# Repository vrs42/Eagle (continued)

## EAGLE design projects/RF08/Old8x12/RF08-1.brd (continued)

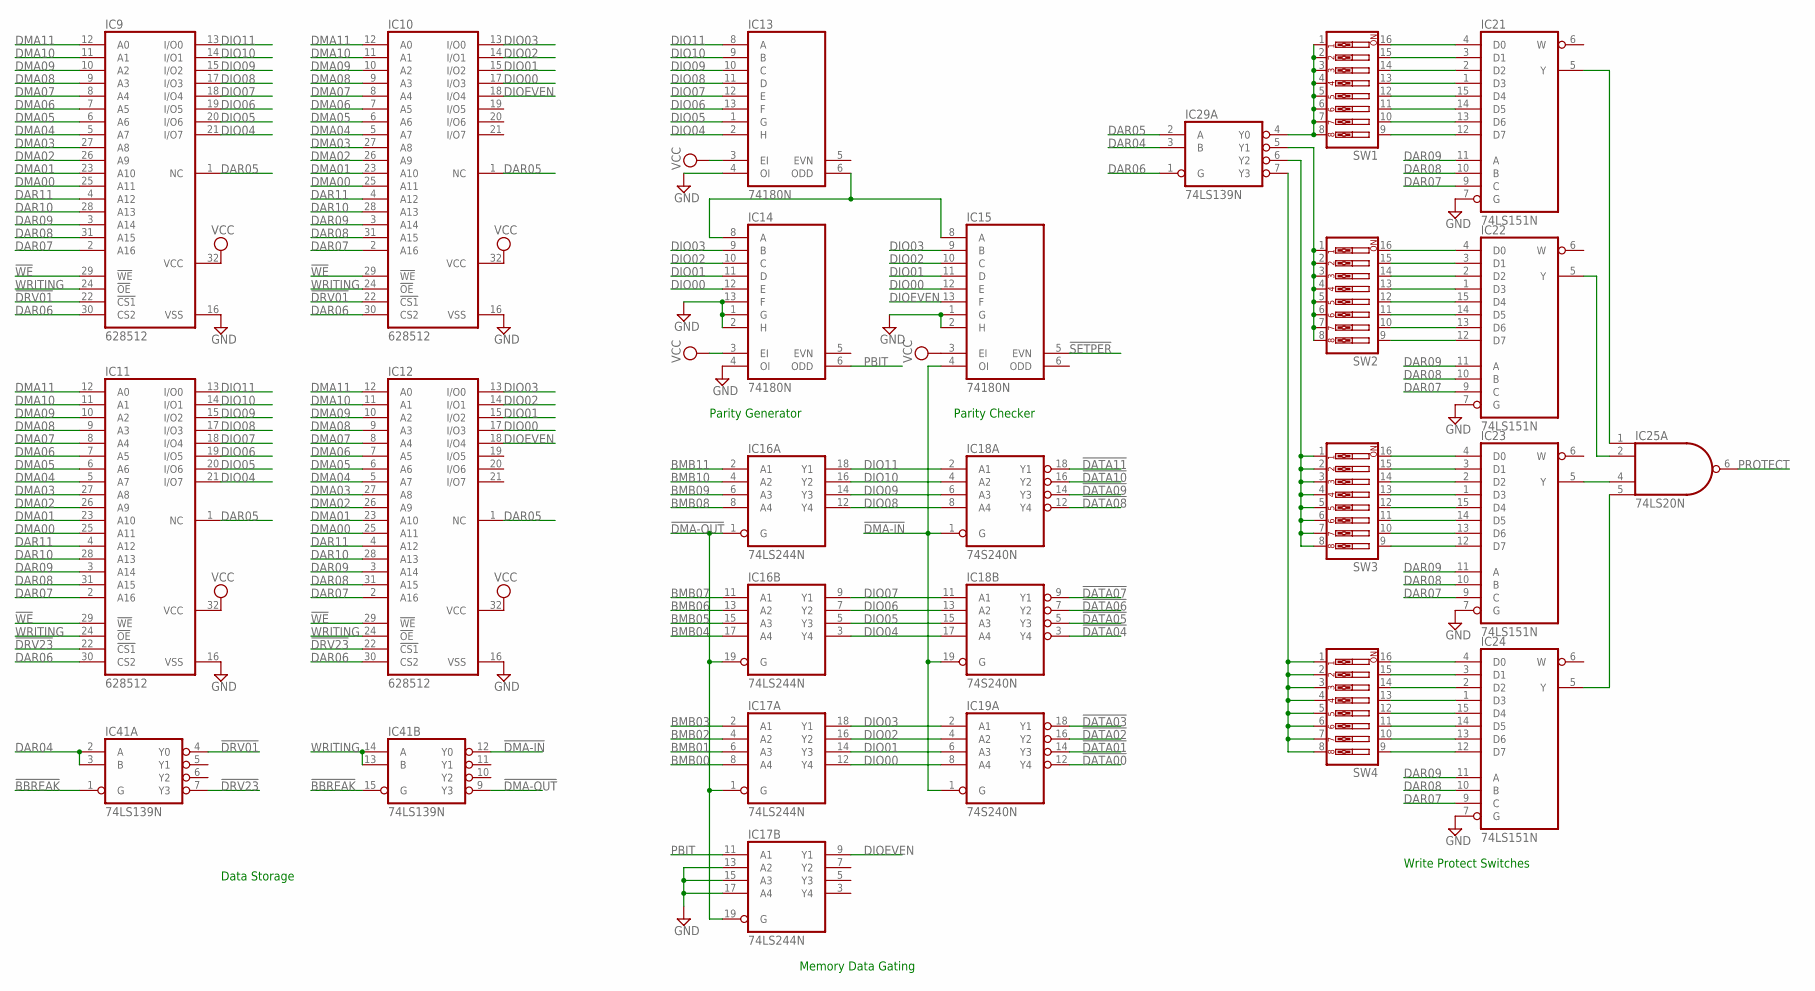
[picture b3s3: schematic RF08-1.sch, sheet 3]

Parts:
IC9, IC10, IC11, IC12: 628512; DIL32
IC13, IC14, IC15: 74180N; DIL14
IC16, IC17: 74LS244N; DIL20
IC18, IC19: 74S240N; DIL20
IC21, IC22, IC23, IC24: 74LS151N; DIL16
IC25: 74LS20N; DIL14
IC29, IC41: 74LS139N; DIL16
SW1, SW2, SW3, SW4: SW_DIP-8; EDG-08

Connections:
!BBREAK: IC41.1 (G), IC41.15 (G); also elsewhere on the board
!DATA00: IC19.12 (Y4); also elsewhere on the board
!DATA01: IC19.14 (Y3); also elsewhere on the board
!DATA02: IC19.16 (Y2); also elsewhere on the board
!DATA03: IC19.18 (Y1); also elsewhere on the board
!DATA04: IC18.3 (Y4); also elsewhere on the board
!DATA05: IC18.5 (Y3); also elsewhere on the board
!DATA06: IC18.7 (Y2); also elsewhere on the board
!DATA07: IC18.9 (Y1); also elsewhere on the board
!DATA08: IC18.12 (Y4); also elsewhere on the board
!DATA09: IC18.14 (Y3); also elsewhere on the board
!DATA10: IC18.16 (Y2); also elsewhere on the board
!DATA11: IC18.18 (Y1); also elsewhere on the board
!DMA-IN: IC15.4 (OI), IC18.1 (G), IC18.19 (G), IC19.1 (G), IC41.12 (Y0)
!DMA-OUT: IC16.1 (G), IC16.19 (G), IC17.1 (G), IC17.19 (G), IC41.9 (Y3)
!DRV01: IC9.22 (!CS1), IC10.22 (!CS1), IC41.4 (Y0)
!DRV23: IC11.22 (!CS1), IC12.22 (!CS1), IC41.7 (Y3)
!SETPER: IC15.5 (EVN); also elsewhere on the board
!WE: IC9.29 (!WE), IC10.29 (!WE), IC11.29 (!WE), IC12.29 (!WE); also elsewhere on the board
BMB00: IC17.8 (A4); also elsewhere on the board
BMB01: IC17.6 (A3); also elsewhere on the board
BMB02: IC17.4 (A2); also elsewhere on the board
BMB03: IC17.2 (A1); also elsewhere on the board
BMB04: IC16.17 (A4); also elsewhere on the board
BMB05: IC16.15 (A3); also elsewhere on the board
BMB06: IC16.13 (A2); also elsewhere on the board
BMB07: IC16.11 (A1); also elsewhere on the board
BMB08: IC16.8 (A4); also elsewhere on the board
BMB09: IC16.6 (A3); also elsewhere on the board
BMB10: IC16.4 (A2); also elsewhere on the board
BMB11: IC16.2 (A1); also elsewhere on the board
DAR04: IC29.3 (B), IC41.2 (A), IC41.3 (B); also elsewhere on the board
DAR05: IC9.1 (NC), IC10.1 (NC), IC11.1 (NC), IC12.1 (NC), IC29.2 (A); also elsewhere on the board
DAR06: IC9.30 (CS2), IC10.30 (CS2), IC11.30 (CS2), IC12.30 (CS2), IC29.1 (G); also elsewhere on the board
DAR07: IC9.2 (A16), IC10.2 (A16), IC11.2 (A16), IC12.2 (A16), IC21.9 (C), IC22.9 (C), IC23.9 (C), IC24.9 (C); also elsewhere on the board
DAR08: IC9.31 (A15), IC10.31 (A15), IC11.31 (A15), IC12.31 (A15), IC21.10 (B), IC22.10 (B), IC23.10 (B), IC24.10 (B); also elsewhere on the board
DAR09: IC9.3 (A14), IC10.3 (A14), IC11.3 (A14), IC12.3 (A14), IC21.11 (A), IC22.11 (A), IC23.11 (A), IC24.11 (A); also elsewhere on the board
DAR10: IC9.28 (A13), IC10.28 (A13), IC11.28 (A13), IC12.28 (A13); also elsewhere on the board
DAR11: IC9.4 (A12), IC10.4 (A12), IC11.4 (A12), IC12.4 (A12); also elsewhere on the board
DIO00: IC10.17 (I/O3), IC12.17 (I/O3), IC14.12 (E), IC15.12 (E), IC17.12 (Y4), IC19.8 (A4)
DIO01: IC10.15 (I/O2), IC12.15 (I/O2), IC14.11 (D), IC15.11 (D), IC17.14 (Y3), IC19.6 (A3)
DIO02: IC10.14 (I/O1), IC12.14 (I/O1), IC14.10 (C), IC15.10 (C), IC17.16 (Y2), IC19.4 (A2)
DIO03: IC10.13 (I/O0), IC12.13 (I/O0), IC14.9 (B), IC15.9 (B), IC17.18 (Y1), IC19.2 (A1)
DIO04: IC9.21 (I/O7), IC11.21 (I/O7), IC13.2 (H), IC16.3 (Y4), IC18.17 (A4)
DIO05: IC9.20 (I/O6), IC11.20 (I/O6), IC13.1 (G), IC16.5 (Y3), IC18.15 (A3)
DIO06: IC9.19 (I/O5), IC11.19 (I/O5), IC13.13 (F), IC16.7 (Y2), IC18.13 (A2)
DIO07: IC9.18 (I/O4), IC11.18 (I/O4), IC13.12 (E), IC16.9 (Y1), IC18.11 (A1)
DIO08: IC9.17 (I/O3), IC11.17 (I/O3), IC13.11 (D), IC16.12 (Y4), IC18.8 (A4)
DIO09: IC9.15 (I/O2), IC11.15 (I/O2), IC13.10 (C), IC16.14 (Y3), IC18.6 (A3)
DIO10: IC9.14 (I/O1), IC11.14 (I/O1), IC13.9 (B), IC16.16 (Y2), IC18.4 (A2)
DIO11: IC9.13 (I/O0), IC11.13 (I/O0), IC13.8 (A), IC16.18 (Y1), IC18.2 (A1)
DIOEVEN: IC10.18 (I/O4), IC12.18 (I/O4), IC15.13 (F), IC17.9 (Y1)
DMA00: IC9.25 (A11), IC10.25 (A11), IC11.25 (A11), IC12.25 (A11); also elsewhere on the board
DMA01: IC9.23 (A10), IC10.23 (A10), IC11.23 (A10), IC12.23 (A10); also elsewhere on the board
DMA02: IC9.26 (A9), IC10.26 (A9), IC11.26 (A9), IC12.26 (A9); also elsewhere on the board
DMA03: IC9.27 (A8), IC10.27 (A8), IC11.27 (A8), IC12.27 (A8); also elsewhere on the board
DMA04: IC9.5 (A7), IC10.5 (A7), IC11.5 (A7), IC12.5 (A7); also elsewhere on the board
DMA05: IC9.6 (A6), IC10.6 (A6), IC11.6 (A6), IC12.6 (A6); also elsewhere on the board
DMA06: IC9.7 (A5), IC10.7 (A5), IC11.7 (A5), IC12.7 (A5); also elsewhere on the board
DMA07: IC9.8 (A4), IC10.8 (A4), IC11.8 (A4), IC12.8 (A4); also elsewhere on the board
DMA08: IC9.9 (A3), IC10.9 (A3), IC11.9 (A3), IC12.9 (A3); also elsewhere on the board
DMA09: IC9.10 (A2), IC10.10 (A2), IC11.10 (A2), IC12.10 (A2); also elsewhere on the board
DMA10: IC9.11 (A1), IC10.11 (A1), IC11.11 (A1), IC12.11 (A1); also elsewhere on the board
DMA11: IC9.12 (A0), IC10.12 (A0), IC11.12 (A0), IC12.12 (A0); also elsewhere on the board
GND: IC9.16 (VSS), IC10.16 (VSS), IC11.16 (VSS), IC12.16 (VSS), IC13.4 (OI), IC13.7 (GND), IC14.1 (G), IC14.2 (H), IC14.4 (OI), IC14.7 (GND), IC14.13 (F), IC15.1 (G), IC15.2 (H), IC15.7 (GND), IC16.10 (GND), IC17.10 (GND), IC17.13 (A2), IC17.15 (A3), IC17.17 (A4), IC18.10 (GND), IC19.10 (GND), IC21.7 (G), IC21.8 (GND), IC22.7 (G), IC22.8 (GND), IC23.7 (G), IC23.8 (GND), IC24.7 (G), IC24.8 (GND), IC25.7 (GND), IC29.8 (GND), IC41.8 (GND); also elsewhere on the board
unnamed: IC29.4 (Y0), SW1.1, SW1.2, SW1.3, SW1.4, SW1.5, SW1.6, SW1.7, SW1.8
unnamed: IC13.6 (ODD), IC14.8 (A), IC15.8 (A)
unnamed: IC22.5 (Y), IC25.2 (I1)
unnamed: IC29.5 (Y1), SW2.1, SW2.2, SW2.3, SW2.4, SW2.5, SW2.6, SW2.7, SW2.8
unnamed: IC29.6 (Y2), SW3.1, SW3.2, SW3.3, SW3.4, SW3.5, SW3.6, SW3.7, SW3.8
unnamed: IC29.7 (Y3), SW4.1, SW4.2, SW4.3, SW4.4, SW4.5, SW4.6, SW4.7, SW4.8
unnamed: IC23.5 (Y), IC25.4 (I2)
unnamed: IC21.5 (Y), IC25.1 (I0)
unnamed: IC24.5 (Y), IC25.5 (I3)
unnamed: IC21.4 (D0), SW1.16
unnamed: IC21.3 (D1), SW1.15
unnamed: IC21.2 (D2), SW1.14
unnamed: IC21.1 (D3), SW1.13
unnamed: IC21.14 (D5), SW1.11
unnamed: IC21.13 (D6), SW1.10
unnamed: IC21.12 (D7), SW1.9
unnamed: IC21.15 (D4), SW1.12
unnamed: IC22.4 (D0), SW2.16
unnamed: IC22.3 (D1), SW2.15
unnamed: IC22.2 (D2), SW2.14
unnamed: IC22.1 (D3), SW2.13
unnamed: IC22.14 (D5), SW2.11
unnamed: IC22.13 (D6), SW2.10
unnamed: IC22.12 (D7), SW2.9
unnamed: IC23.4 (D0), SW3.16
unnamed: IC23.3 (D1), SW3.15
unnamed: IC23.2 (D2), SW3.14
unnamed: IC23.1 (D3), SW3.13
unnamed: IC23.14 (D5), SW3.11
unnamed: IC23.13 (D6), SW3.10
unnamed: IC23.12 (D7), SW3.9
unnamed: IC24.4 (D0), SW4.16
unnamed: IC24.3 (D1), SW4.15
unnamed: IC24.2 (D2), SW4.14
unnamed: IC24.1 (D3), SW4.13
unnamed: IC24.14 (D5), SW4.11
unnamed: IC24.13 (D6), SW4.10
unnamed: IC24.12 (D7), SW4.9
unnamed: IC24.15 (D4), SW4.12
unnamed: IC23.15 (D4), SW3.12
unnamed: IC22.15 (D4), SW2.12
PBIT: IC14.6 (ODD), IC17.11 (A1)
PROTECT: IC25.6 (O); also elsewhere on the board
VCC: IC9.32 (VCC), IC10.32 (VCC), IC11.32 (VCC), IC12.32 (VCC), IC13.3 (EI), IC13.14 (VCC), IC14.3 (EI), IC14.14 (VCC), IC15.3 (EI), IC15.14 (VCC), IC16.20 (VCC), IC17.20 (VCC), IC18.20 (VCC), IC19.20 (VCC), IC21.16 (VCC), IC22.16 (VCC), IC23.16 (VCC), IC24.16 (VCC), IC25.14 (VCC), IC29.16 (VCC), IC41.16 (VCC); also elsewhere on the board
WRITING: IC9.24 (!OE), IC10.24 (!OE), IC11.24 (!OE), IC12.24 (!OE), IC41.13 (B), IC41.14 (A); also elsewhere on the board

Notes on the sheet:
Parity Generator
Parity Checker
Memory Data Gating
Write Protect Switches
Data Storage

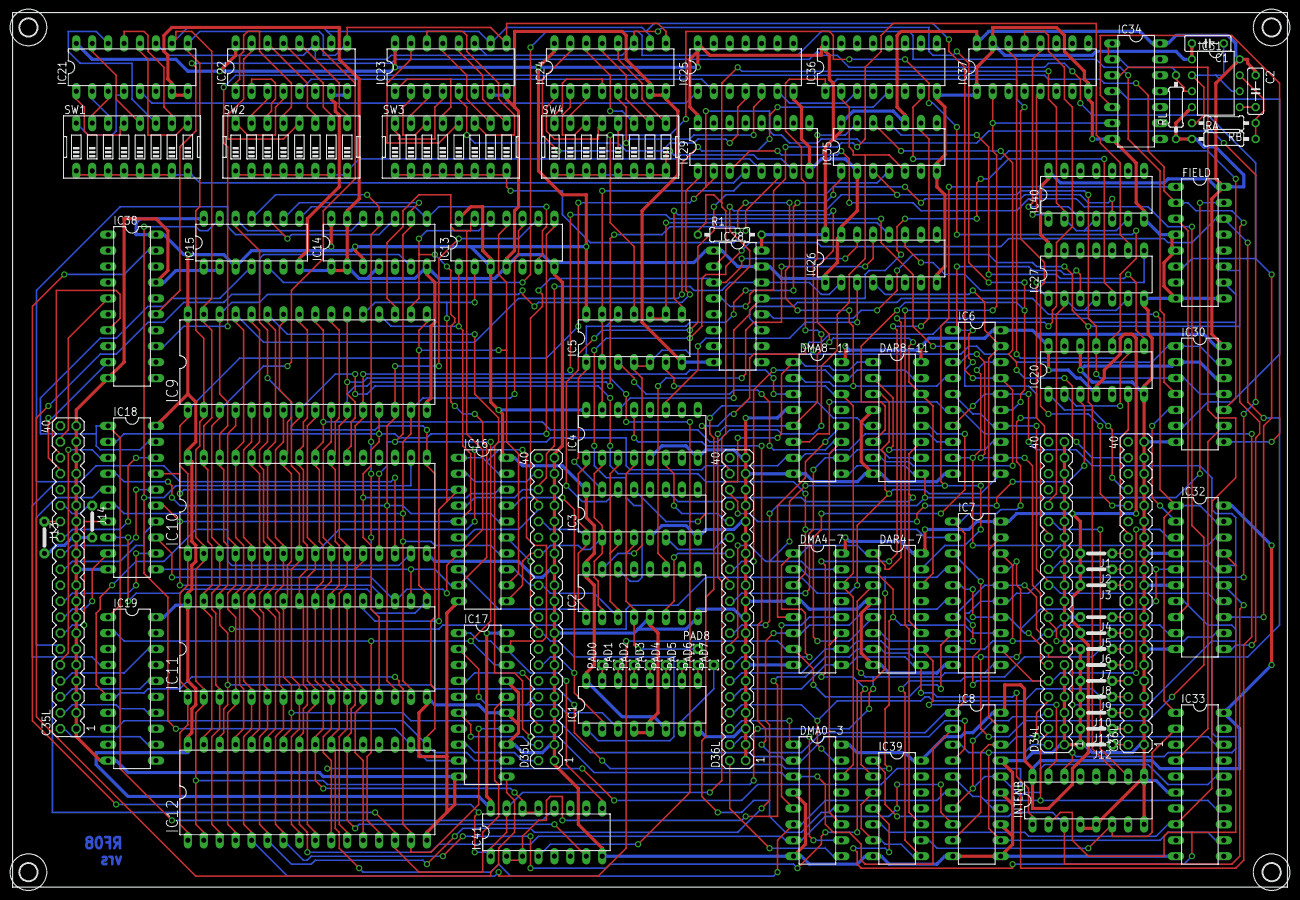
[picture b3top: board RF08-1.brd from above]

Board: 2 copper layers, 203.2 x 139.4 mm, 90 parts (0 on the bottom side), 221 nets.

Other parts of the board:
U$1, U$2, U$3, U$4: 2,8

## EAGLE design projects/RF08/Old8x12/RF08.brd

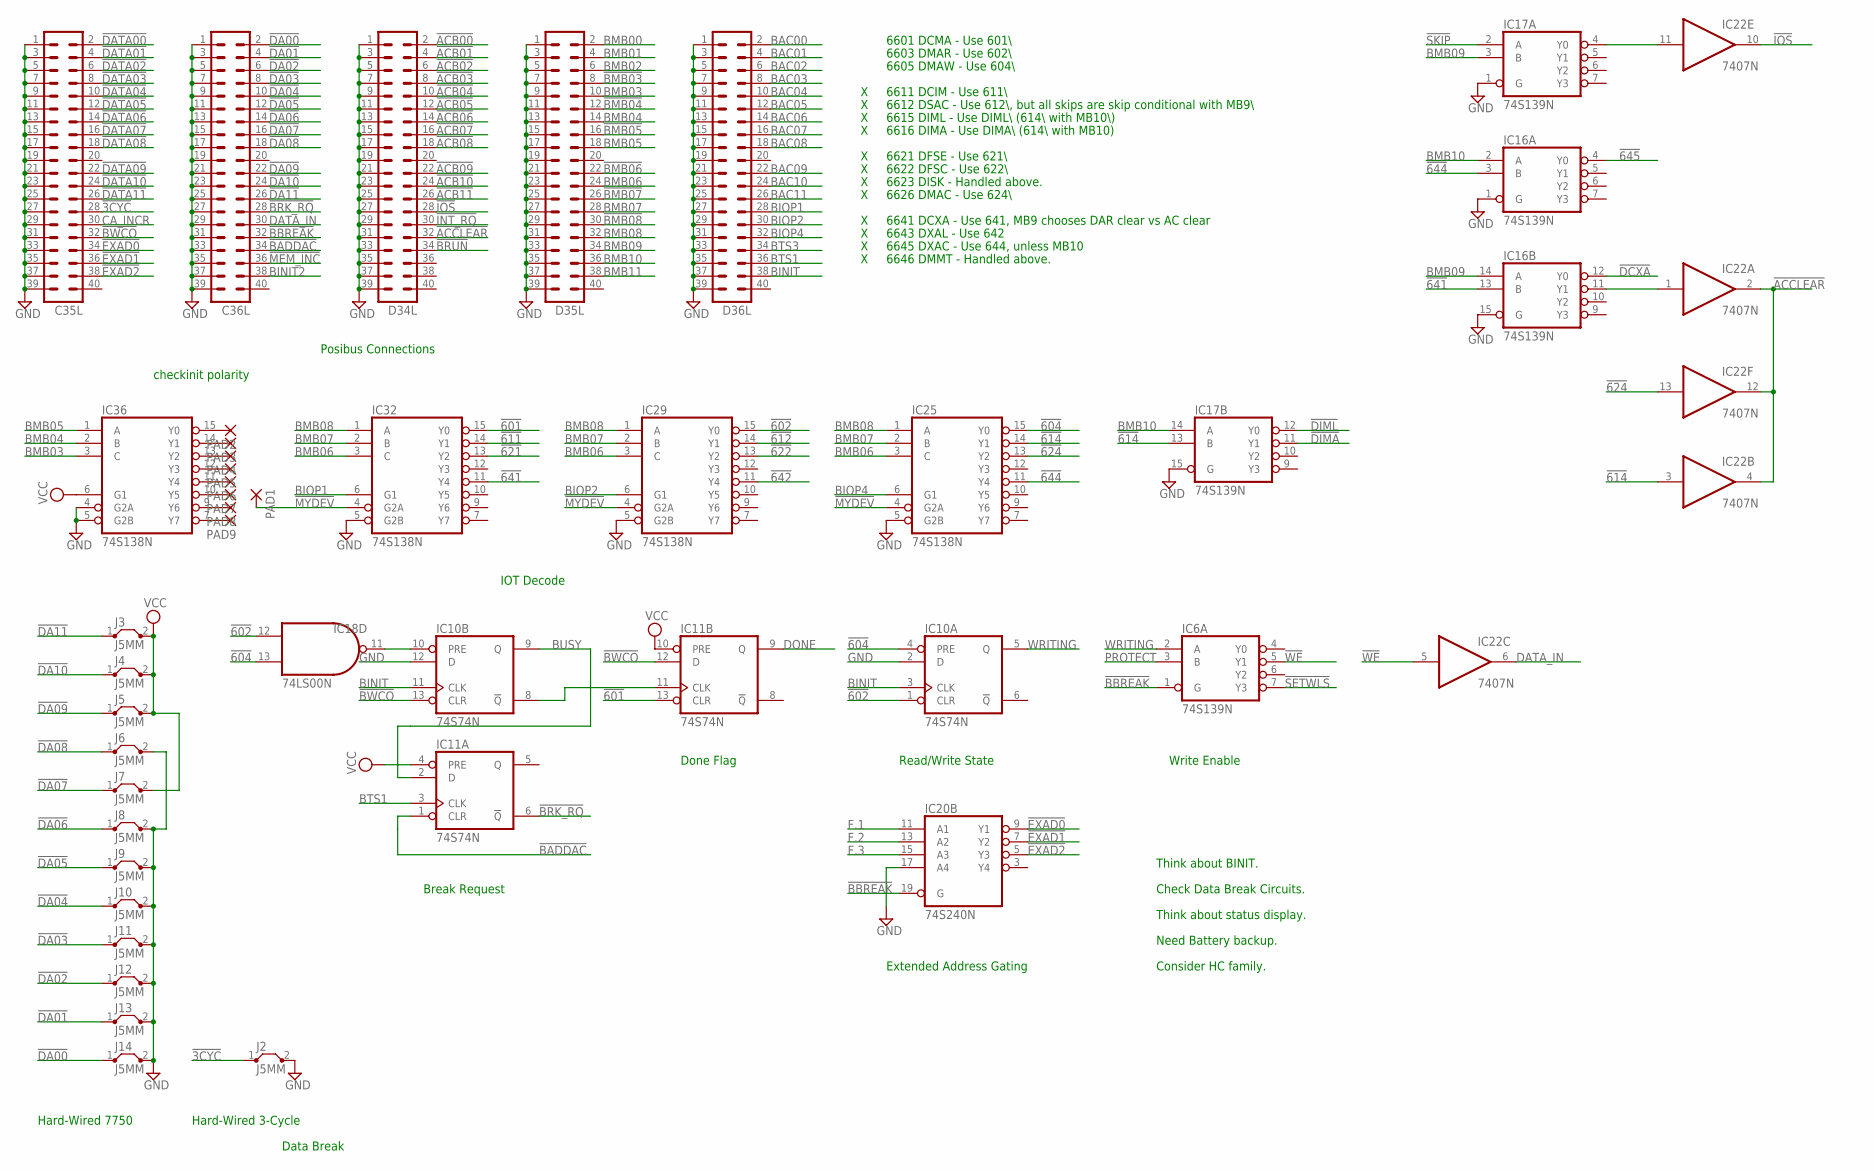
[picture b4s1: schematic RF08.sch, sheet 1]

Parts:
C35L, C36L: MA20-2
D34L, D35L, D36L: MA20-2
IC6, IC16, IC17: 74S139N; DIL16
IC10, IC11: 74S74N; DIL14
IC18: 74LS00N; DIL14
IC20: 74S240N; DIL20
IC22: 7407N; DIL14
IC25, IC29, IC32, IC36: 74S138N; DIL16
J2, J3, J4, J5, J6, J7, J8, J9, J10, J11, J12, J13, J14: J5MM; 05
PAD1, PAD2, PAD3, PAD4, PAD5, PAD6, PAD7, PAD8, PAD9: 1,6/0,8

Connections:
!3CYC: C35L.28, J2.1
!601: IC11.13 (CLR), IC32.15 (Y0); also elsewhere on the board
!602: IC10.1 (CLR), IC18.12 (I0), IC29.15 (Y0); also elsewhere on the board
!604: IC10.4 (PRE), IC18.13 (I1), IC25.15 (Y0); also elsewhere on the board
!611: IC32.14 (Y1); also elsewhere on the board
!612: IC29.14 (Y1); also elsewhere on the board
!614: IC17.13 (B), IC22.3 (I), IC25.14 (Y1)
!621: IC32.13 (Y2); also elsewhere on the board
!622: IC29.13 (Y2); also elsewhere on the board
!624: IC22.13 (I), IC25.13 (Y2); also elsewhere on the board
!641: IC16.13 (B), IC32.11 (Y4)
!642: IC29.11 (Y4); also elsewhere on the board
!644: IC16.3 (B), IC25.11 (Y4)
!645: IC16.4 (Y0); also elsewhere on the board
!ACB00: D34L.2; also elsewhere on the board
!ACB01: D34L.4; also elsewhere on the board
!ACB02: D34L.6; also elsewhere on the board
!ACB03: D34L.8; also elsewhere on the board
!ACB04: D34L.10; also elsewhere on the board
!ACB05: D34L.12; also elsewhere on the board
!ACB06: D34L.14; also elsewhere on the board
!ACB07: D34L.16; also elsewhere on the board
!ACB08: D34L.18; also elsewhere on the board
!ACB09: D34L.22; also elsewhere on the board
!ACB10: D34L.24; also elsewhere on the board
!ACB11: D34L.26; also elsewhere on the board
!ACCLEAR: D34L.32, IC22.2 (O), IC22.4 (O), IC22.12 (O)
!BADDAC: C36L.34, IC11.1 (CLR)
!BBREAK: C36L.32, IC6.1 (G), IC20.19 (G); also elsewhere on the board
!BMB03: D35L.8
!BMB04: D35L.12
!BMB05: D35L.16
!BMB06: D35L.22
!BMB07: D35L.26
!BMB08: D35L.30
!BRK_RQ: C36L.28, IC11.6 (!Q)
!BRUN: D34L.34
!BWCO: C35L.32, IC10.13 (CLR), IC11.12 (D)
!DA00: C36L.2, J14.1
!DA01: C36L.4, J13.1
!DA02: C36L.6, J12.1
!DA03: C36L.8, J11.1
!DA04: C36L.10, J10.1
!DA05: C36L.12, J9.1
!DA06: C36L.14, J8.1
!DA07: C36L.16, J7.1
!DA08: C36L.18, J6.1
!DA09: C36L.22, J5.1
!DA10: C36L.24, J4.1
!DA11: C36L.26, J3.1
!DATA00: C35L.2; also elsewhere on the board
!DATA01: C35L.4; also elsewhere on the board
!DATA02: C35L.6; also elsewhere on the board
!DATA03: C35L.8; also elsewhere on the board
!DATA04: C35L.10; also elsewhere on the board
!DATA05: C35L.12; also elsewhere on the board
!DATA06: C35L.14; also elsewhere on the board
!DATA07: C35L.16; also elsewhere on the board
!DATA08: C35L.18; also elsewhere on the board
!DATA09: C35L.22; also elsewhere on the board
!DATA10: C35L.24; also elsewhere on the board
!DATA11: C35L.26; also elsewhere on the board
!DCXA: IC16.12 (Y0); also elsewhere on the board
!DIMA: IC17.11 (Y1); also elsewhere on the board
!DIML: IC17.12 (Y0); also elsewhere on the board
!EXAD0: C35L.34, IC20.9 (Y1)
!EXAD1: C35L.36, IC20.7 (Y2)
!EXAD2: C35L.38, IC20.5 (Y3)
!INT_RQ: D34L.30; also elsewhere on the board
!IOS: D34L.28, IC22.10 (O)
!MEM_INC: C36L.36
!MYDEV: IC25.4 (G2A), IC29.4 (G2A), IC32.4 (G2A), PAD1.1
!SETWLS: IC6.7 (Y3); also elsewhere on the board
!SKIP: IC17.2 (A); also elsewhere on the board
!WE: IC6.5 (Y1), IC22.5 (I); also elsewhere on the board
BAC00: D36L.2; also elsewhere on the board
BAC01: D36L.4; also elsewhere on the board
BAC02: D36L.6; also elsewhere on the board
BAC03: D36L.8; also elsewhere on the board
BAC04: D36L.10; also elsewhere on the board
BAC05: D36L.12; also elsewhere on the board
BAC06: D36L.14; also elsewhere on the board
BAC07: D36L.16; also elsewhere on the board
BAC08: D36L.18; also elsewhere on the board
BAC09: D36L.22; also elsewhere on the board
BAC10: D36L.24; also elsewhere on the board
BAC11: D36L.26; also elsewhere on the board
BINIT: D36L.38, IC10.3 (CLK), IC10.11 (CLK); also elsewhere on the board
BINIT2: C36L.38
BIOP1: D36L.28, IC32.6 (G1)
BIOP2: D36L.30, IC29.6 (G1)
BIOP4: D36L.32, IC25.6 (G1)
BMB00: D35L.2; also elsewhere on the board
BMB01: D35L.4; also elsewhere on the board
BMB02: D35L.6; also elsewhere on the board
BMB03: D35L.10, IC36.3 (C); also elsewhere on the board
BMB04: D35L.14, IC36.2 (B); also elsewhere on the board
BMB05: D35L.18, IC36.1 (A); also elsewhere on the board
BMB06: D35L.24, IC25.3 (C), IC29.3 (C), IC32.3 (C); also elsewhere on the board
BMB07: D35L.28, IC25.2 (B), IC29.2 (B), IC32.2 (B); also elsewhere on the board
BMB08: D35L.32, IC25.1 (A), IC29.1 (A), IC32.1 (A); also elsewhere on the board
BMB09: D35L.34, IC16.14 (A), IC17.3 (B); also elsewhere on the board
BMB10: D35L.36, IC16.2 (A), IC17.14 (A); also elsewhere on the board
BMB11: D35L.38; also elsewhere on the board
BTS1: D36L.36, IC11.3 (CLK)
BTS3: D36L.34
BUSY: IC10.9 (Q), IC11.2 (D); also elsewhere on the board
CA_INCR: C35L.30
DATA_IN: C36L.30, IC22.6 (O)
DONE: IC11.9 (Q); also elsewhere on the board
F.1: IC20.11 (A1); also elsewhere on the board
F.2: IC20.13 (A2); also elsewhere on the board
F.3: IC20.15 (A3); also elsewhere on the board
GND: C35L.1, C35L.3, C35L.5, C35L.7, C35L.9, C35L.11, C35L.13, C35L.15, C35L.17, C35L.19, C35L.21, C35L.23, C35L.25, C35L.27, C35L.29, C35L.31, C35L.33, C35L.35, C35L.37, C35L.39, C36L.1, C36L.3, C36L.5, C36L.7, C36L.9, C36L.11, C36L.13, C36L.15, C36L.17, C36L.19, C36L.21, C36L.23, C36L.25, C36L.27, C36L.29, C36L.31, C36L.33, C36L.35, C36L.37, C36L.39, D34L.1, D34L.3, D34L.5, D34L.7, D34L.9, D34L.11, D34L.13, D34L.15, D34L.17, D34L.19, D34L.21, D34L.23, D34L.25, D34L.27, D34L.29, D34L.31, D34L.33, D34L.35, D34L.37, D34L.39, D35L.1, D35L.3, D35L.5, D35L.7, D35L.9, D35L.11, D35L.13, D35L.15, D35L.17, D35L.19, D35L.21, D35L.23, D35L.25, D35L.27, D35L.29, D35L.31, D35L.33, D35L.35, D35L.37, D35L.39, D36L.1, D36L.3, D36L.5, D36L.7, D36L.9, D36L.11, D36L.13, D36L.15, D36L.17, D36L.19, D36L.21, D36L.23, D36L.25, D36L.27, D36L.29, D36L.31, D36L.33, D36L.35, D36L.37, D36L.39, IC6.8 (GND), IC10.2 (D), IC10.7 (GND), IC10.12 (D), IC11.7 (GND), IC16.1 (G), IC16.8 (GND), IC16.15 (G), IC17.1 (G), IC17.8 (GND), IC17.15 (G), IC18.7 (GND), IC20.10 (GND), IC20.17 (A4), IC22.7 (GND), IC25.5 (G2B), IC25.8 (GND), IC29.5 (G2B), IC29.8 (GND), IC32.5 (G2B), IC32.8 (GND), IC36.4 (G2A), IC36.5 (G2B), IC36.8 (GND), J2.2, J6.2, J8.2, J9.2, J10.2, J11.2, J12.2, J13.2, J14.2; also elsewhere on the board
unnamed: IC36.9 (Y6), PAD8.1
unnamed: IC10.8 (!Q), IC11.11 (CLK)
unnamed: IC36.15 (Y0), PAD2.1
unnamed: IC36.14 (Y1), PAD3.1
unnamed: IC36.13 (Y2), PAD4.1
unnamed: IC36.12 (Y3), PAD5.1
unnamed: IC36.11 (Y4), PAD6.1
unnamed: IC36.10 (Y5), PAD7.1
unnamed: IC36.7 (Y7), PAD9.1
unnamed: IC16.11 (Y1), IC22.1 (I)
unnamed: IC17.4 (Y0), IC22.11 (I)
unnamed: IC10.10 (PRE), IC18.11 (O)
PROTECT: IC6.3 (B); also elsewhere on the board
VCC: IC6.16 (VCC), IC10.14 (VCC), IC11.4 (PRE), IC11.10 (PRE), IC11.14 (VCC), IC16.16 (VCC), IC17.16 (VCC), IC18.14 (VCC), IC20.20 (VCC), IC22.14 (VCC), IC25.16 (VCC), IC29.16 (VCC), IC32.16 (VCC), IC36.6 (G1), IC36.16 (VCC), J3.2, J4.2, J5.2, J7.2; also elsewhere on the board
WRITING: IC6.2 (A), IC10.5 (Q); also elsewhere on the board

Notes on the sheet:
6601 DCMA - Use 601\\
6603 DMAR - Use 602\\
6605 DMAW - Use 604\\
6611 DCIM - Use 611\\
6612 DSAC - Use 612\\, but all skips are skip conditional with MB9\\
6615 DIML - Use DIML\\ (614\\ with MB10\\)
6616 DIMA - Use DIMA\\ (614\\ with MB10)
6621 DFSE - Use 621\\
6622 DFSC - Use 622\\
6623 DISK - Handled above.
6626 DMAC - Use 624\\
6641 DCXA - Use 641, MB9 chooses DAR clear vs AC clear
6643 DXAL - Use 642
6645 DXAC - Use 644, unless MB10
6646 DMMT - Handled above.
Posibus Connections
IOT Decode
Data Break
Hard-Wired 7750
Hard-Wired 3-Cycle
Think about BINIT.
Think about status display.
Break Request
Need Battery backup.
Done Flag
Extended Address Gating
Read/Write State
Write Enable
Check Data Break Circuits.
Consider HC family.
checkinit polarity

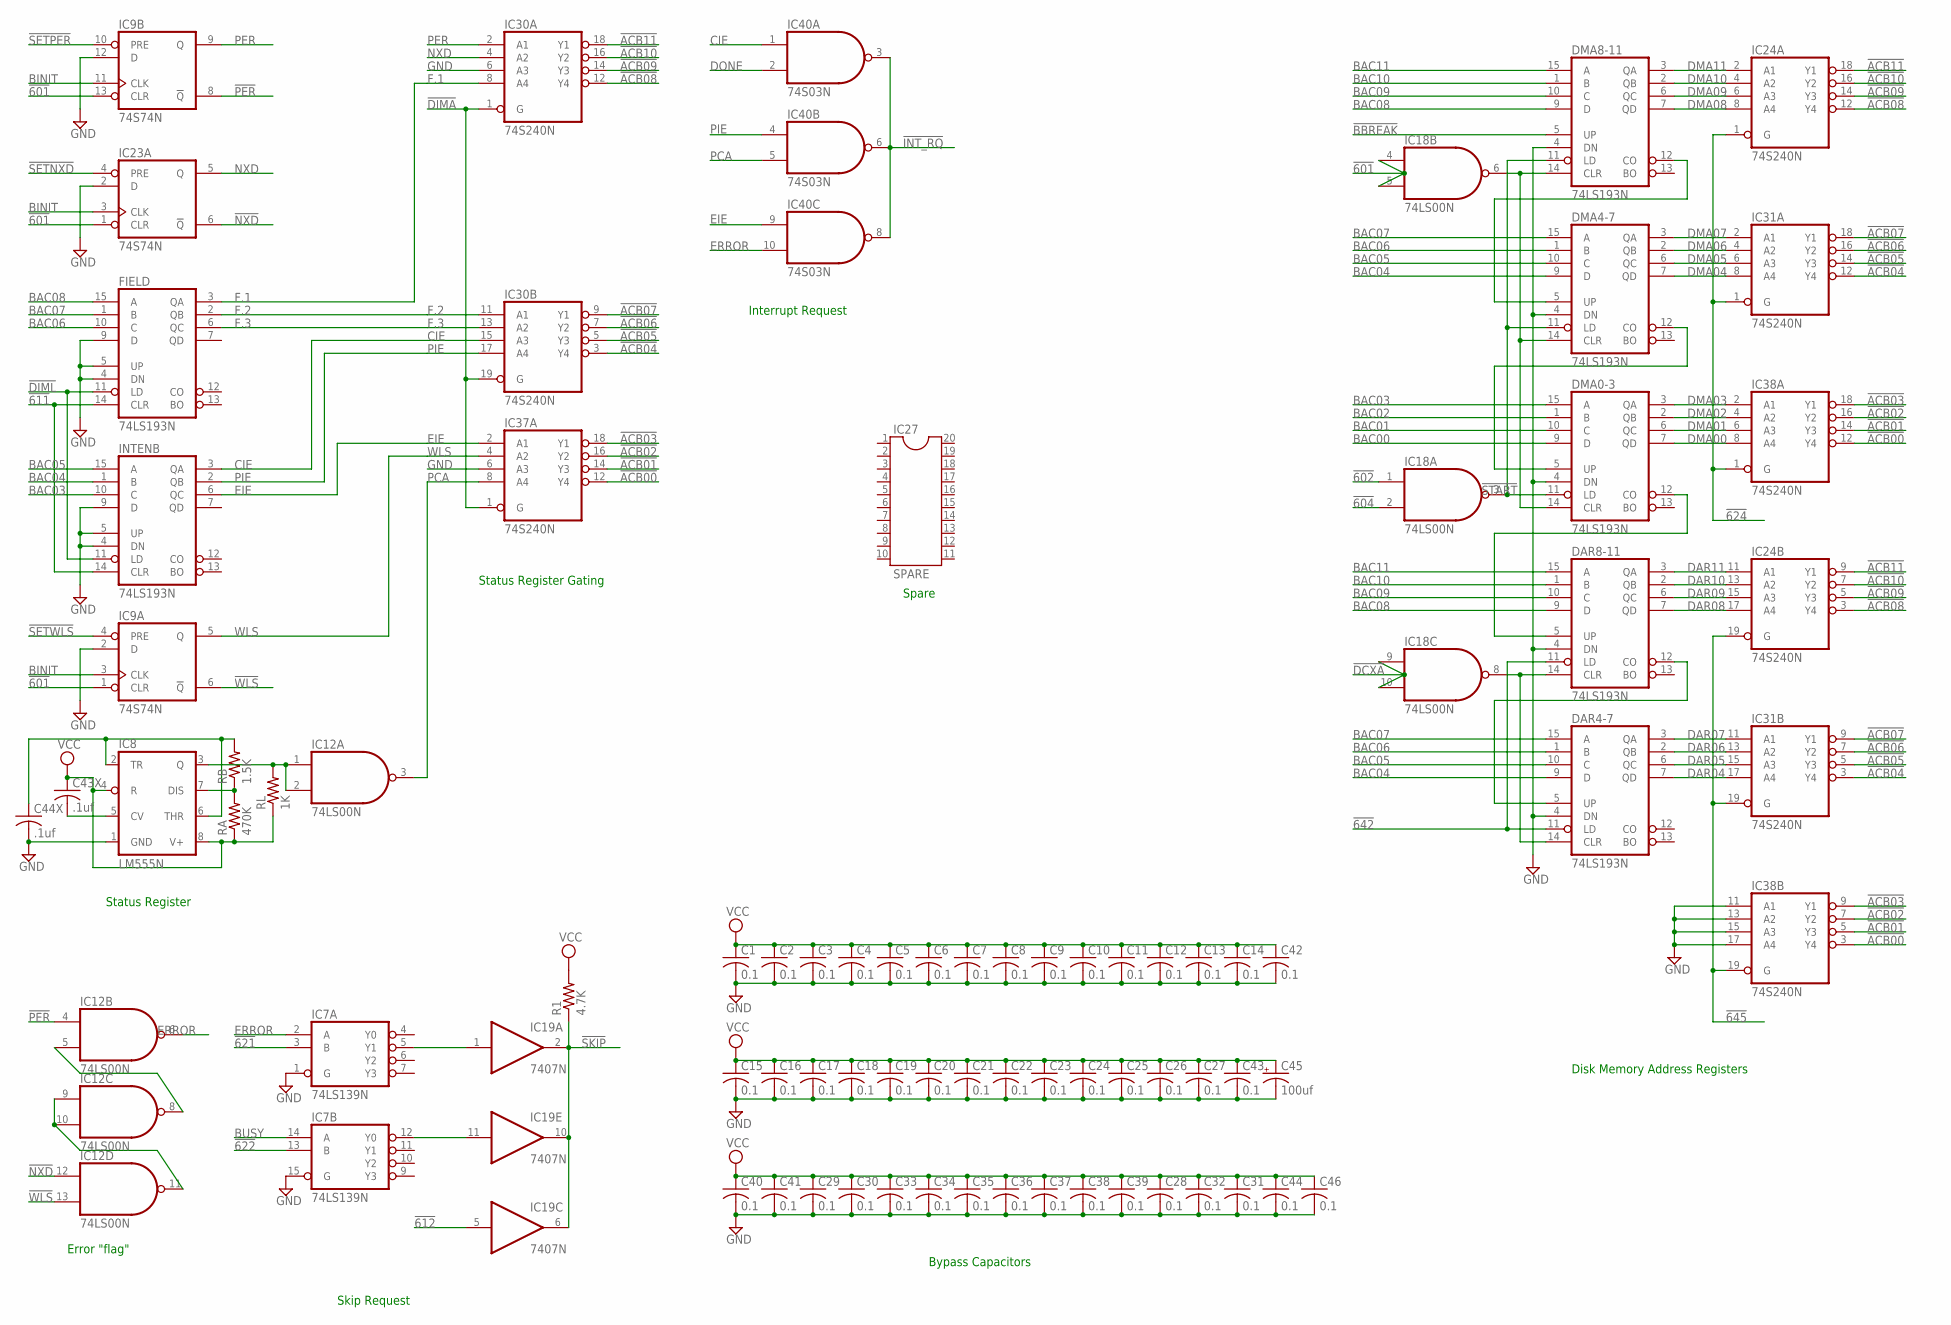
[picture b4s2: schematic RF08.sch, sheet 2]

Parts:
C1, C2, C3, C4, C5, C6, C7, C8, C9, C10, C11, C12, C13, C14, C15, C16, C17, C18, C19, C20, C21, C22, C23, C24, C25, C26, C27, C28, C29, C30, C31, C32, C33, C34, C35, C36, C37, C38, C39, C40, C41, C42, C43, C44, C46: 0.1; C050-025X075
C43X, C44X: .1uf; C050-025X075
C45: 100uf; E22-6
DAR4-7, DAR8-11: 74LS193N; DIL16
DMA0-3, DMA4-7, DMA8-11: 74LS193N; DIL16
FIELD: 74LS193N; DIL16
IC7: 74LS139N; DIL16
IC8: LM555N; DIL08
IC9, IC23: 74S74N; DIL14
IC12, IC18: 74LS00N; DIL14
IC19: 7407N; DIL14
IC24, IC30, IC31, IC37, IC38: 74S240N; DIL20
IC27: SPARE; DIL20
IC40: 74S03N; DIL14
INTENB: 74LS193N; DIL16
R1: 4.7K; 0207/10
RA: 470K; 0207/10
RB: 1.5K; 0207/10
RL: 1K; 0207/10

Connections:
!601: IC9.1 (CLR), IC9.13 (CLR), IC18.4 (I0), IC18.5 (I1), IC23.1 (CLR); also elsewhere on the board
!602: IC18.1 (I0); also elsewhere on the board
!604: IC18.2 (I1); also elsewhere on the board
!611: FIELD.14 (CLR), INTENB.14 (CLR); also elsewhere on the board
!612: IC19.5 (I); also elsewhere on the board
!621: IC7.3 (B); also elsewhere on the board
!622: IC7.13 (B); also elsewhere on the board
!624: IC24.1 (G), IC31.1 (G), IC38.1 (G); also elsewhere on the board
!642: DAR4-7.11 (LD), DAR8-11.11 (LD); also elsewhere on the board
!645: IC24.19 (G), IC31.19 (G), IC38.19 (G); also elsewhere on the board
!ACB00: IC37.12 (Y4), IC38.3 (Y4), IC38.12 (Y4); also elsewhere on the board
!ACB01: IC37.14 (Y3), IC38.5 (Y3), IC38.14 (Y3); also elsewhere on the board
!ACB02: IC37.16 (Y2), IC38.7 (Y2), IC38.16 (Y2); also elsewhere on the board
!ACB03: IC37.18 (Y1), IC38.9 (Y1), IC38.18 (Y1); also elsewhere on the board
!ACB04: IC30.3 (Y4), IC31.3 (Y4), IC31.12 (Y4); also elsewhere on the board
!ACB05: IC30.5 (Y3), IC31.5 (Y3), IC31.14 (Y3); also elsewhere on the board
!ACB06: IC30.7 (Y2), IC31.7 (Y2), IC31.16 (Y2); also elsewhere on the board
!ACB07: IC30.9 (Y1), IC31.9 (Y1), IC31.18 (Y1); also elsewhere on the board
!ACB08: IC24.3 (Y4), IC24.12 (Y4), IC30.12 (Y4); also elsewhere on the board
!ACB09: IC24.5 (Y3), IC24.14 (Y3), IC30.14 (Y3); also elsewhere on the board
!ACB10: IC24.7 (Y2), IC24.16 (Y2), IC30.16 (Y2); also elsewhere on the board
!ACB11: IC24.9 (Y1), IC24.18 (Y1), IC30.18 (Y1); also elsewhere on the board
!BBREAK: DMA8-11.5 (UP); also elsewhere on the board
!DCXA: IC18.9 (I0), IC18.10 (I1); also elsewhere on the board
!DIMA: IC30.1 (G), IC30.19 (G), IC37.1 (G); also elsewhere on the board
!DIML: FIELD.11 (LD), INTENB.11 (LD); also elsewhere on the board
!INT_RQ: IC40.3 (O), IC40.6 (O), IC40.8 (O); also elsewhere on the board
!NXD: IC12.12 (I0), IC23.6 (!Q)
!PER: IC9.8 (!Q), IC12.4 (I0)
!SETNXD: IC23.4 (PRE); also elsewhere on the board
!SETPER: IC9.10 (PRE); also elsewhere on the board
!SETWLS: IC9.4 (PRE); also elsewhere on the board
!SKIP: IC19.2 (O), IC19.6 (O), IC19.10 (O), R1.1; also elsewhere on the board
!START: DMA0-3.11 (LD), DMA4-7.11 (LD), DMA8-11.11 (LD), IC18.3 (O)
!WLS: IC9.6 (!Q), IC12.13 (I1)
BAC00: DMA0-3.9 (D); also elsewhere on the board
BAC01: DMA0-3.10 (C); also elsewhere on the board
BAC02: DMA0-3.1 (B); also elsewhere on the board
BAC03: DMA0-3.15 (A), INTENB.10 (C); also elsewhere on the board
BAC04: DAR4-7.9 (D), DMA4-7.9 (D), INTENB.1 (B); also elsewhere on the board
BAC05: DAR4-7.10 (C), DMA4-7.10 (C), INTENB.15 (A); also elsewhere on the board
BAC06: DAR4-7.1 (B), DMA4-7.1 (B), FIELD.10 (C); also elsewhere on the board
BAC07: DAR4-7.15 (A), DMA4-7.15 (A), FIELD.1 (B); also elsewhere on the board
BAC08: DAR8-11.9 (D), DMA8-11.9 (D), FIELD.15 (A); also elsewhere on the board
BAC09: DAR8-11.10 (C), DMA8-11.10 (C); also elsewhere on the board
BAC10: DAR8-11.1 (B), DMA8-11.1 (B); also elsewhere on the board
BAC11: DAR8-11.15 (A), DMA8-11.15 (A); also elsewhere on the board
BINIT: IC9.3 (CLK), IC9.11 (CLK), IC23.3 (CLK); also elsewhere on the board
BUSY: IC7.14 (A); also elsewhere on the board
CIE: IC30.15 (A3), IC40.1 (I0), INTENB.3 (QA)
DAR04: DAR4-7.7 (QD), IC31.17 (A4); also elsewhere on the board
DAR05: DAR4-7.6 (QC), IC31.15 (A3); also elsewhere on the board
DAR06: DAR4-7.2 (QB), IC31.13 (A2); also elsewhere on the board
DAR07: DAR4-7.3 (QA), IC31.11 (A1); also elsewhere on the board
DAR08: DAR8-11.7 (QD), IC24.17 (A4); also elsewhere on the board
DAR09: DAR8-11.6 (QC), IC24.15 (A3); also elsewhere on the board
DAR10: DAR8-11.2 (QB), IC24.13 (A2); also elsewhere on the board
DAR11: DAR8-11.3 (QA), IC24.11 (A1); also elsewhere on the board
DMA00: DMA0-3.7 (QD), IC38.8 (A4); also elsewhere on the board
DMA01: DMA0-3.6 (QC), IC38.6 (A3); also elsewhere on the board
DMA02: DMA0-3.2 (QB), IC38.4 (A2); also elsewhere on the board
DMA03: DMA0-3.3 (QA), IC38.2 (A1); also elsewhere on the board
DMA04: DMA4-7.7 (QD), IC31.8 (A4); also elsewhere on the board
DMA05: DMA4-7.6 (QC), IC31.6 (A3); also elsewhere on the board
DMA06: DMA4-7.2 (QB), IC31.4 (A2); also elsewhere on the board
DMA07: DMA4-7.3 (QA), IC31.2 (A1); also elsewhere on the board
DMA08: DMA8-11.7 (QD), IC24.8 (A4); also elsewhere on the board
DMA09: DMA8-11.6 (QC), IC24.6 (A3); also elsewhere on the board
DMA10: DMA8-11.2 (QB), IC24.4 (A2); also elsewhere on the board
DMA11: DMA8-11.3 (QA), IC24.2 (A1); also elsewhere on the board
DONE: IC40.2 (I1); also elsewhere on the board
EIE: IC37.2 (A1), IC40.9 (I0), INTENB.6 (QC)
ERROR: IC7.2 (A), IC12.6 (O), IC40.10 (I1)
F.1: FIELD.3 (QA), IC30.8 (A4); also elsewhere on the board
F.2: FIELD.2 (QB), IC30.11 (A1); also elsewhere on the board
F.3: FIELD.6 (QC), IC30.13 (A2); also elsewhere on the board
GND: C1.2, C2.2, C3.2, C4.2, C5.2, C6.2, C7.2, C8.2, C9.2, C10.2, C11.2, C12.2, C13.2, C14.2, C15.2, C16.2, C17.2, C18.2, C19.2, C20.2, C21.2, C22.2, C23.2, C24.2, C25.2, C26.2, C27.2, C28.2, C29.2, C30.2, C31.2, C32.2, C33.2, C34.2, C35.2, C36.2, C37.2, C38.2, C39.2, C40.2, C41.2, C42.2, C43.2, C44.2, C44X.2, C45.-, C46.2, DAR4-7.4 (DN), DAR4-7.8 (GND), DAR8-11.4 (DN), DAR8-11.8 (GND), DMA0-3.4 (DN), DMA0-3.8 (GND), DMA4-7.4 (DN), DMA4-7.8 (GND), DMA8-11.4 (DN), DMA8-11.8 (GND), FIELD.4 (DN), FIELD.5 (UP), FIELD.8 (GND), FIELD.9 (D), IC7.1 (G), IC7.8 (GND), IC7.15 (G), IC8.1 (GND), IC9.2 (D), IC9.7 (GND), IC9.12 (D), IC12.7 (GND), IC18.7 (GND), IC19.7 (GND), IC23.2 (D), IC23.7 (GND), IC24.10 (GND), IC30.6 (A3), IC30.10 (GND), IC31.10 (GND), IC37.6 (A3), IC37.10 (GND), IC38.10 (GND), IC38.11 (A1), IC38.13 (A2), IC38.15 (A3), IC38.17 (A4), IC40.7 (GND), INTENB.4 (DN), INTENB.5 (UP), INTENB.8 (GND), INTENB.9 (D); also elsewhere on the board
unnamed: DMA0-3.5 (UP), DMA4-7.12 (CO)
unnamed: DAR4-7.14 (CLR), DAR8-11.14 (CLR), IC18.8 (O)
unnamed: DMA4-7.5 (UP), DMA8-11.12 (CO)
unnamed: DAR8-11.5 (UP), DMA0-3.12 (CO)
unnamed: DMA0-3.14 (CLR), DMA4-7.14 (CLR), DMA8-11.14 (CLR), IC18.6 (O)
unnamed: DAR4-7.5 (UP), DAR8-11.12 (CO)
unnamed: IC7.5 (Y1), IC19.1 (I)
unnamed: IC8.7 (DIS), RA.2, RB.1
unnamed: IC8.3 (Q), IC12.1 (I0), IC12.2 (I1), RL.2
unnamed: C44X.1, IC8.2 (TR), IC8.6 (THR), RB.2
unnamed: IC7.12 (Y0), IC19.11 (I)
unnamed: C43X.2, IC8.5 (CV)
unnamed: IC12.9 (I0), IC12.10 (I1), IC12.11 (O)
unnamed: IC12.5 (I1), IC12.8 (O)
NXD: IC23.5 (Q), IC30.4 (A2)
PCA: IC12.3 (O), IC37.8 (A4), IC40.5 (I1)
PER: IC9.9 (Q), IC30.2 (A1)
PIE: IC30.17 (A4), IC40.4 (I0), INTENB.2 (QB)
VCC: C1.1, C2.1, C3.1, C4.1, C5.1, C6.1, C7.1, C8.1, C9.1, C10.1, C11.1, C12.1, C13.1, C14.1, C15.1, C16.1, C17.1, C18.1, C19.1, C20.1, C21.1, C22.1, C23.1, C24.1, C25.1, C26.1, C27.1, C28.1, C29.1, C30.1, C31.1, C32.1, C33.1, C34.1, C35.1, C36.1, C37.1, C38.1, C39.1, C40.1, C41.1, C42.1, C43.1, C43X.1, C44.1, C45.+, C46.1, DAR4-7.16 (VCC), DAR8-11.16 (VCC), DMA0-3.16 (VCC), DMA4-7.16 (VCC), DMA8-11.16 (VCC), FIELD.16 (VCC), IC7.16 (VCC), IC8.4 (R), IC8.8 (V+), IC9.14 (VCC), IC12.14 (VCC), IC18.14 (VCC), IC19.14 (VCC), IC23.14 (VCC), IC24.20 (VCC), IC30.20 (VCC), IC31.20 (VCC), IC37.20 (VCC), IC38.20 (VCC), IC40.14 (VCC), INTENB.16 (VCC), R1.2, RA.1, RL.1; also elsewhere on the board
WLS: IC9.5 (Q), IC37.4 (A2)

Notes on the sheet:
Disk Memory Address Registers
Status Register
Status Register Gating
Interrupt Request
Error "flag"
Skip Request
Spare
Bypass Capacitors
